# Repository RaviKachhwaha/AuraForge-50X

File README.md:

<h1 align="center">
  <br>

  <br>
  AuraForge-50X
  <br>
</h1>
<h3 align="center">
A fully open-sourced complete wireless sound computer. 
</h3>

| Front Render | Back Render | 
| --- | --- |
|  |  | 

## Schematics  

Here are the schematic design,

## Features
- **ESP32-WROOM-32E MCU** - Dual-core Xtensa LX6, adjustable from 80 MHz to 240 MHz.
- **A 50Hz Wi-Fi CSI radar and real time DSP**.
- **TPA3116D2 Class-D amp**.
- **3A fast charging with BMS and Li-ion/LiPo both Battery support**.
- Power and battery indicator LED.
- Cyberpunk Web HUD.
- **USB C** - for programming.
- A 12-21V DC jack for power.

## PCB Design 
|  |
|--- |  

 ### The PCB is 4 layers with dimensions 100x80mm, made to be easily useable for anyone.  

 ### All the PCB files are [here](https://github.com/RaviKachhwaha/AuraForge-50X/blob/main/hardware) 

| Front Layer | Inner Layer 1 |
| --- | --- |
|  |  |
| Inner Layer 2 | Bottom layer |
|  |  |

## Pinout  

This is a general pinout 

|  | 
| --- | 

## 3D image of board case 

This is a 3D view screenshot of case for board.

|  | 
| --- | 

## 3D image of speakers case 

This is a 3D view screenshot of case for speakers.

|  | 
| --- | 

Note :- I not use 3D printing for case of speakers and not added to BOM list due to the cost is very high but if any one want to get this 3D they will get files in 3D files folder.

(Credits to the KiCad EDA for KICAD 10, Espressif Systems for the MCU, RuView for CSI processing and Hack Club for fund to make this possible.) 

(Thanks to Madhav, tty7 to review my Design and tell me some mistakes like the antenna is pleased on board without open air due to that the range of it is low after the review from them I places the antenna in open air to get full range of Bluetooth and correct Wi-Fi CSI) 

## Why was it made?  

While using the normal Bluetooth amp for my many projects and in daily need, I realised it doesn't have Wi-Fi and high power support and I couldn't use it, unfortunately I had to think to buy a different high power amp then I see that those have high power but not Wi-Fi support and use very low price components which give low quality, but now I designed one with the simplicity of ESP32-WROOM-32E with being able to use Wi-Fi and Bluetooth both and also Programing support in a same board with high quality audio support for amp IC and have too many features.

## How you can get one for yourself? 

That is pretty easy, you have all the files you will need in the production folder, order the development  
board from any PCB fab ( I chose PCB Power cause its cheap in India and has good quality and also made in India ) and BINGO! You will have it to use for any purpose you want!  

## How do you use it?  
You can use it as any normal amp board but first want to flash the firmware which is given in firmware folder, for flashing you need to first enter the boootloader mode by holding the BOOT buttom and one time press and release the RESET button while connecting to your device, flash it with firmware and after all flashing done press the RESET button one time and you are good to go!
I have attached a simple firmware to start with prebuild firmware available in the firmware folder.  

## BOM  
|Name|Purpose          |Quantity|Total Cost (USD)|Link               |Distributor|
|----|-----------------|--------|----------------|-------------------|-----------|
|PCBA|Board and Assembly|2       |62.12           |[Lion Circuits](lioncircuits.com)|Lion Circuits     |
|Electronic Components|BOM Component Sourcing|2       |117.00           |[Lion Circuits](lioncircuits.com)|Lion Circuits     |
|2 Components|2 BOM Component Sourcing which is not got from Lion Circuits|2       |2.59           |[Sharvi Electronics](sharvielectronics.com)|Sharvi Electronics     |
|Battery|18650 3.7V 3000mAh Li-ion Battery with Connector for testing|1       |5.00          |[18650 Battery](https://www.amazon.in/gp/product/B0HBPWY1CS/ref=ox_sc_act_title_3?smid=AJWV8HAM5L3YL&psc=1)|Amazon India     |
|Speaker|5 Inch 4 Ohm 25W Full-Range Woofer Speaker (Stereo Pair) for testing|1       |5.48           |[5 Inch Speaker](https://www.amazon.in/gp/product/B0D8CVNZVK/ref=ox_sc_act_title_2?smid=A3C7Z4RVM9A3G1&psc=1)| Amazon India     |
|Data & Power Cable|100W USB-C to USB-C Silicone Cable (3ft / 1.0m) for uploading firmware|1       |5.00           |[USB-C Cable](https://www.amazon.in/gp/product/B0F316KC1Q/ref=ox_sc_act_title_4?smid=AJ6SIZC8YQDZX&psc=1)| Amazon India     |
|Speaker connection Cable|20 Meter speaker wiring Cable (64ft / 20.0m) for connecting the speakers and testing|1       |3.10           |[20 Meter Wire](https://www.amazon.in/gp/product/B0CHBFB5H2/ref=ox_sc_act_title_1?smid=A2LH9DQUAZIHP2&psc=1)| Amazon India     |
|Aux Cable|5 Meter Aux Cable for testing the 3.5 mm Aux jack and wired audio input system|1       |2.70           |[5 Meter Aux Cable](https://www.amazon.in/gp/product/B08XBFV4VR/ref=ox_sc_act_title_2?smid=A2LH9DQUAZIHP2&psc=1)| Amazon India     |
|Power Supply|20 Volt Power supply to run the board on its high power to test all things is working on its full power|1       |5.55           |[20V Power Supply](https://www.amazon.in/gp/product/B0D22W62W9/ref=ox_sc_act_title_1?smid=A2QFGJBWFSGOIU&psc=1)| Amazon India     |
|Cable to give power to power supply|1.5 Meter Power Cable to give power to power supply adapter due to it not have cable with it|1       |1.60           |[Main Power cable](https://www.amazon.in/gp/product/B0F9VD5NC5/ref=ox_sc_act_title_1?smid=AJ6SIZC8YQDZX&psc=1)| Amazon India     |
|3D Printing|3D printing of cases of board only|2       |17.00           |[3D Printing Service](https://3ding.in)|3Ding    |
|MDF Board |MDF board to make speakers cases|1       |2.65           |[MDF Board](https://www.amazon.in/gp/product/B09PLC82L1/ref=ox_sc_act_image_3?smid=A1URIIGAKCXMM9&psc=1)| Amazon India    |
|Fevicol|Fevicol to joint the MDF boards and make cases|1       |1.10           |[Fevicol](https://www.amazon.in/gp/product/B0FR92PQHL/ref=ox_sc_act_image_1?smid=AJ6SIZC8YQDZX&psc=1)| Amazon India    |
|Soldering Iron |Temperature controlled soldering iron to solder the 2 IC's come from Sharvi Electronics on both boards with Flux paste and extra soldering bits tips to get SMD level small tip and tweezers to hold the IC over its place without burning fingers and some other small needed items|1       |5.10           |[Soldering Iron](https://www.amazon.in/gp/product/B09Q1DNJMH/ref=ox_sc_act_image_2?smid=A1ABQHFG9A1NPH&psc=1)| Amazon India    |
|Paint |Paint is needed to paint the MDF board cases and making its life long and best quality|1       |2.25           |[Paint](https://www.amazon.in/gp/product/B08G54WH1J/ref=ox_sc_act_image_1?smid=AJ6SIZC8YQDZX&psc=1)| Amazon India    |
|Breathable Knitted Air Mesh Polyester Fabric |Net to place over the speaker case front to cover the speaker and making the case best and complete| 1       |3.10           |[Speaker Front Net](https://www.amazon.in/gp/product/B0GX12PGCJ/ref=ox_sc_act_image_2?smid=A3B565BTI4IG0&psc=1)| Amazon India    |
|24V DC RS795 Large Torque High Power Universal Motor |This is needed to cut the MDF board in required size and for hole's in MDF speaker case| 1       |3.75           |[RS795](https://www.amazon.in/gp/product/B0DVSYSMTV/ref=ox_sc_act_image_7?smid=A3C7Z4RVM9A3G1&psc=1)| Amazon India    |
|Drill Chuck For 775 Motor |This is needed to connect the cutter blades and drill bits to the RS795 motor| 1       |4.25           |[Drill Chuck](https://www.amazon.in/gp/product/B09FSN8MWR/ref=ox_sc_act_image_8?smid=AGBMZOA8TJT82&psc=1)| Amazon India    |
|HSS Circular Saw Blade/Cutting Discs Set |This is to connect in Motor and cut the MDF board in needed shape's| 1       |2.25           |[Cutting Discs](https://www.amazon.in/gp/product/B07BT39DQT/ref=ox_sc_act_image_6?smid=A14ZM8X9CLFWBZ&psc=1)| Amazon India    |
|0.3-1.6mm Shank Twist Drill Bit Set |This Drill bits is to make holes for speaker screws to fit speaker in case's| 1       |2.50           |[Drill Bit's](https://www.amazon.in/gp/product/B09CGPJSRG/ref=ox_sc_act_image_5?smid=A22JYHMKEZ67RF&psc=1)| Amazon India    |
|Adjustable Wood Hole saw Circle drill bit |This is a adjustable wood cutter (30-200mm) to cut 5 inch speaker circle hole in MDF board for speakers case's| 1       |3.65           |[Circle drill bit](https://www.amazon.in/gp/product/B0GV7VG341/ref=ox_sc_act_image_4?smid=AVW5MVBH0F2Y1&psc=1)| Amazon India    |
|5-piece CYL-1 Masonry Drill Bit Set |These are big size drill bit's to make big holes for wires and etc. in MDF speaker case's| 1       |2.75           |[Big Drill Bit's](https://www.amazon.in/gp/product/B00863NRHQ/ref=ox_sc_act_image_3?smid=AJ6SIZC8YQDZX&psc=1)| Amazon India    |
|Safety Gloves |These are for heavy duty cutting and drilling time safety and also safety from spray paint during MDF speaker cases painting and coating| 1       |3.85           |[Safety Gloves](https://www.amazon.in/gp/product/B0CHFP47WB/ref=ox_sc_act_image_2?smid=AB4PAYFSMOP1X&psc=1)| Amazon India    |
|Safety Mask with Respirator |This is for safety of eyes during spray paint and cutting and drilling and also safety of respiratory system from spray paint gas's and small particles of MDF during cutting and drilling| 1       |5.75           |[Safety Mask](https://www.amazon.in/gp/product/B0GCSJ1299/ref=ox_sc_act_image_1?smid=A2X8WL6YI17S5T&psc=1)| Amazon India    |
| | | Total | 270.80 |

LCSC & DigiKey BOM for the components on board is [here](https://github.com/RaviKachhwaha/AuraForge-50X/blob/main/components_bom.csv)

!!Thanks to ALL!!

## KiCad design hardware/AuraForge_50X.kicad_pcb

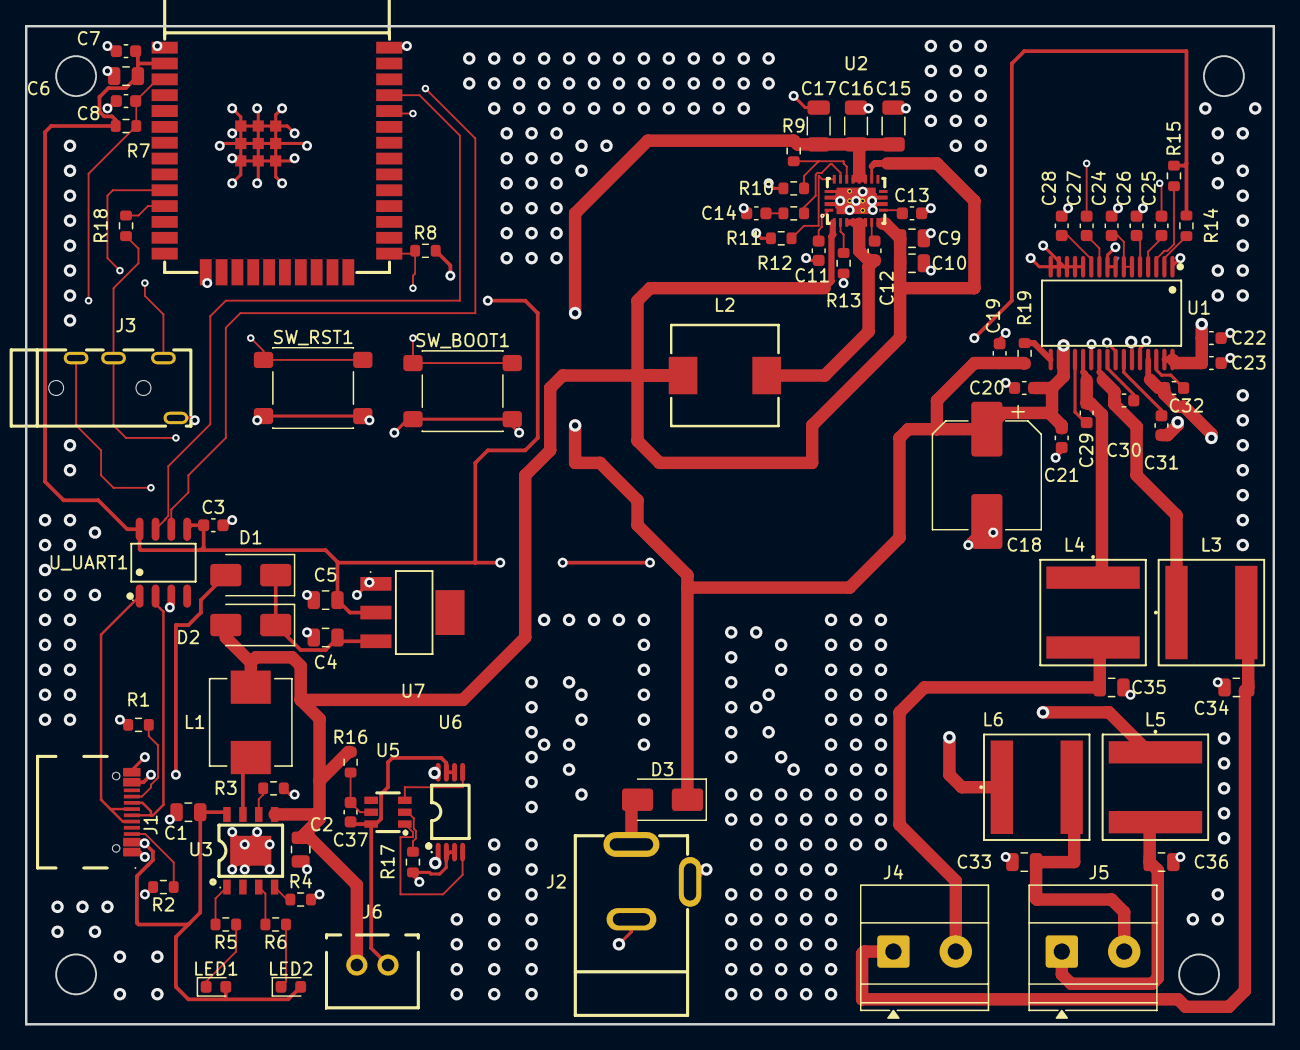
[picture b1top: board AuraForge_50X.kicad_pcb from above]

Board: 4 copper layers, 100.0 x 80.0 mm, 83 parts (0 on the bottom side), 61 nets.

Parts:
C1: 10uF 25V; C_0805_2012Metric
C2, C9, C10: 22uF 10V; C_0805_2012Metric
C3, C7, C8, C37: 100nF 16V; C_0603_1608Metric
C4: 10uF 16V; C_0805_2012Metric
C5: 22uF 6.3V; C_0805_2012Metric
C6: 10uF 10V; C_0805_2012Metric
C11, C24, C25, C26, C27, C28: 1uF 16V; C_0603_1608Metric
C12: 100nF 25V; C_0603_1608Metric
C13: 10nF 25V; C_0603_1608Metric
C14: 2.2nF 25V; C_0603_1608Metric
C15, C16, C17: 22uF 25V; C_1206_3216Metric
C18: 220uF 25V Low-ESR; CP_Elec_8x10.5
C19, C20, C21, C22, C23: 1uF 25V; C_0603_1608Metric
C29, C30, C31, C32: 0.22uF 25V; C_0603_1608Metric
C33, C34, C35, C36: 0.68uF 25V; C_0805_2012Metric
D1, D2, D3: SS34; D_SMA
J1: TYPE-C-31-M-12; USB-C_SMD-TYPE-C-31-M-12_1
J2: PJ-002AH; DC-IN-TH_PJ-002AH
J3: PJ-320A; AUDIO-TH_XKB_PJ-320A
J4: Speaker_Left; TerminalBlock_Phoenix_MKDS-1,5-2_1x02_P5.00mm_Horizontal
J5: Speaker_Right; TerminalBlock_Phoenix_MKDS-1,5-2_1x02_P5.00mm_Horizontal
J6: B2B-XH-A; CONN-TH_B2B-XH-A-LF-SN
L1: 2.2uH 6.5A; INDM7066X300N
L2: 2.2uH 10A; WE-HCC_8070
L3, L4, L5, L6: 10uH 3.8A; IND_TAIYO_NRS8040_TAY
LED1: RED; LED_0603_1608Metric
LED2: Green; LED_0603_1608Metric
R1, R2: 5.1k; R_0603_1608Metric
R3: 45k 1%; R_0603_1608Metric
R4: 51k; R_0603_1608Metric
R5, R6, R17, R18: 1k; R_0603_1608Metric
R7, R8, R11: 10k; R_0603_1608Metric
R9: 91k 1%; R_0603_1608Metric
R10: 10k 1%; R_0603_1608Metric
R12, R14, R15: 100k; R_0603_1608Metric
R13: 120k; R_0603_1608Metric
R16: 100R; R_0603_1608Metric
R19: 10R; R_0603_1608Metric
SW_BOOT1: BOOT; SW_SPST_PTS645Sx43SMTR92
SW_RST1: RESET; SW_SPST_PTS645Sx43SMTR92
U1: TPA3116D2DAD; HTSSOP-32_L11.0-W6.1-P0.65-LS8.1-BL
U2: TPS61088RHLR; VQFN-20_L4.6-W3.6-P0.50-BL
U3: IP2312-4V35; ESOP-8_L4.9-W3.9-P1.27-LS6.0-BL-EP
U4: ESP32-WROOM-32E; WIFI-SMD_ESP32-WROOM-32E
U5: DW01A-G; SOT-23-6_L2.9-W1.6-P0.95-LS2.8-BR
U6: FS8205A; TSSOP-8_L4.4-W3.0-P0.65-LS6.4-BL-2
U7: AMS1117-3.3; SOT-223-3_L6.5-W3.4-P2.30-LS7.0-BR
U_UART1: CH340N_C2977777; SOP-8_L4.9-W3.9-P1.27-LS6.0-BL

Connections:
/+3V3_SYS: C3.1, C5.2, C6.2, C7.2, R7.1, R8.2, R14.1, R15.1, U4.2 (3V3), U7.2 (VOUT), U_UART1.5 (VCC), U_UART1.8 (V3)
/+5V_VBUS: C1.1, D1.2 (A), J1.A4B9 (VBUS), J1.B4A9 (VBUS), LED1.2 (A), LED2.2 (A), U3.8 (VIN)
/+21V_BOOST: C15.1, C16.1, C17.1, C18.1, C19.1, C20.1, C21.1, C22.1, C23.1, D3.1 (K), R9.2, R19.1, U1.18 (PVCC), U1.19 (PVCC), U1.31 (PVCC), U1.32 (PVCC), U2.14 (VOUT), U2.15 (VOUT), U2.16 (VOUT)
/+BAT_3V7: C2.1, C9.1, C10.2, D2.2 (A), J6.1, L1.2, L2.1, R16.2, U2.2 (EN), U2.9 (VIN), U2.13 (MODE), U3.5 (BAT)
/AUDIO_L: C27.1, J3.2
/AUDIO_R: C25.1, J3.3, R18.1
/BAT_NEG: C37.1, J6.2, U5.6 (GND), U6.6 (S2), U6.7 (S2)
/DAC_OUT_L: J3.4, U4.10 (IO25)
/DAC_OUT_R: R18.2, U4.11 (IO26)
/ESP_EN: C8.2, R7.2, SW_RST1.1, U4.3 (EN)
/ESP_IO0: R8.1, SW_BOOT1.1, U4.25 (IO0)
/ESP_RXD0: U4.34 (RXD0), U_UART1.6 (TXD)
/ESP_TXD0: U4.35 (TXD0), U_UART1.7 (RXD)
/SPK_L_MINUS: C35.1, J4.2, L4.2
/SPK_L_PLUS: C34.1, J4.1, L3.2
/SPK_R_MINUS: C33.1, J5.2, L6.2
/SPK_R_PLUS: C36.1, J5.1, L5.2
/USB_DN: J1.A7 (DN1), J1.B7 (DN2), U_UART1.2 (UD-)
/USB_DP: J1.A6 (DP1), J1.B6 (DP2), U_UART1.1 (UD+)
/V_LDO_IN: C4.2, D1.1 (K), D2.1 (K), U7.3 (VIN)
GND: C1.2, C2.2, C3.2, C4.1, C5.1, C6.1, C7.1, C8.1, C9.2, C10.1, C11.1, C13.2, C14.2, C15.2, C16.2, C17.2, C18.2, C19.2, C20.2, C21.2, C22.2, C23.2, C24.1, C26.1, C28.1, C33.2, C34.2, C35.2, C36.2, J1.A1B12 (GND), J1.B1A12 (GND), J2.2, J2.3, J3.5, R1.2, R2.2, R3.2, R4.2, R10.2, R12.1, R13.1, R17.2, SW_BOOT1.2, SW_RST1.2, U1.1 (MODSEL), U1.8 (GAIN/SLV), U1.9 (GND), U1.12 (MUTE), U1.13 (AM2), U1.14 (AM1), U1.15 (AM0), U1.16 (SYNC), U1.22 (GND), U1.25 (GND), U1.28 (GND), U2.20 (AGND), U2.21 (PGND), U3.9 (EP), U4.1 (GND), U4.15 (GND), U4.38 (GND), U4.39 (GND), U6.2 (S1), U6.3 (S1), U7.1 (GND), U_UART1.3 (GND)
unnamed: C12.2, L2.2, U2.4 (SW), U2.5 (SW), U2.6 (SW), U2.7 (SW)
unnamed: C14.1, R11.2
unnamed: D3.2 (A), J2.1
unnamed: J1.A5 (CC1), R1.1
unnamed: J1.B5 (CC2), R2.1
unnamed: LED1.1 (K), R5.1
unnamed: LED2.1 (K), R6.1
unnamed: R19.2, U1.17 (AVCC)
unnamed: C29.2, U1.20 (BSNL)
unnamed: C31.2, U1.26 (BSNR)
unnamed: C30.1, U1.24 (BSPL)
unnamed: C32.1, U1.30 (BSPR)
unnamed: R15.2, U1.3 (FAULTZ)
unnamed: C24.2, U1.6 (PLIMIT), U1.7 (GVDD)
unnamed: C28.2, U1.11 (LINN)
unnamed: C27.2, U1.10 (LINP)
unnamed: C29.1, L4.1, U1.21 (OUTNL)
unnamed: C31.1, L6.1, U1.27 (OUTNR)
unnamed: C30.2, L3.1, U1.23 (OUTPL)
unnamed: C32.2, L5.1, U1.29 (OUTPR)
unnamed: C26.2, U1.5 (RINN)
unnamed: C25.2, U1.4 (RINP)
unnamed: R14.2, U1.2 (SDZ)
unnamed: C12.1, U2.8 (BOOT)
unnamed: R11.1, U2.18 (COMP)
unnamed: R9.1, R10.1, U2.17 (FB)
unnamed: R13.2, U2.3 (FSW)
unnamed: R12.2, U2.19 (ILIM)
unnamed: C13.1, U2.10 (SS)
unnamed: C11.2, U2.1 (VCC)
unnamed: R5.2, U3.1 (D1)
unnamed: R6.2, U3.3 (D2)
unnamed: R3.1, U3.6 (ICHG)
unnamed: R4.1, U3.4 (NTC)
unnamed: L1.1, U3.7 (SW)
unnamed: R17.1, U5.2 (CS)
unnamed: U5.3 (OC), U6.5 (G2)
unnamed: U5.1 (OD), U6.4 (G1)
unnamed: C37.2, R16.1, U5.5 (VCC)
unnamed: U6.1 (D12), U6.8 (D12)

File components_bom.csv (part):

Item #,Reference,Qty,Value,Description,Footprint,Manufacturer,MPN,LCSC Part,Unit Price (₹),Unit Price ($),Total Price (₹),Total Price ($),Supplier Link
1,C1,1,10uF 25V,MLCC Ceramic Capacitor 10uF 25V X7S 0805 for Boost/Buck Input Filtering,Capacitor_SMD:C_0805_2012Metric,TDK,C2012X7S1E106K125AC,,56.37,0.5911,56.37,0.59,https://www.digikey.in/en/products/detail/tdk/C2012X7S1E106K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
2,"C2, C9, C10",3,22uF 10V,MLCC Ceramic Capacitor 22uF 10V X5R 0805 for 3.3V/5V Rail Bulk Decoupling,Capacitor_SMD:C_0805_2012Metric,Yageo,CC0805MKX5R6BB226,,44.91,0.4709,134.73,1.41,https://www.digikey.in/en/products/detail/yageo/CC0805MKX5R6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
3,"C3, C7, C8, C37",4,100nF 16V,MLCC Ceramic Capacitor 100nF 16V X7R 0603 High-Frequency Bypass Decoupling,Capacitor_SMD:C_0603_1608Metric,Yageo,CC0603KRX7R7BB104,,9.56,0.1002,38.24,0.40,https://www.digikey.in/en/products/detail/yageo/CC0603KRX7R7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
4,C4,1,10uF 16V,MLCC Ceramic Capacitor 10uF 16V X5R 0805 Power Rail Decoupling,Capacitor_SMD:C_0805_2012Metric,Yageo,CC0805KRX5R7BB106,,60.20,0.6312,60.20,0.63,https://www.digikey.in/en/products/detail/yageo/CC0805KRX5R7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
5,C5,1,22uF 6.3V,MLCC Ceramic Capacitor 22uF 6.3V X5R 0805 Low-Voltage Rail Filter,Capacitor_SMD:C_0805_2012Metric,Yageo,CC0805MKX5R5BB226,,40.13,0.4208,40.13,0.42,https://www.digikey.in/en/products/detail/yageo/CC0805MKX5R5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
6,C6,1,10uF 10V,MLCC Ceramic Capacitor 10uF 10V X5R 0805 LDO Output Filter,Capacitor_SMD:C_0805_2012Metric,Yageo,CC0805KRX5R6BB106,,51.60,0.5411,51.60,0.54,https://www.digikey.in/en/products/detail/yageo/CC0805KRX5R6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
7,"C11, C24, C25, C26, C27, C28",6,1uF 16V,MLCC Ceramic Capacitor 1uF 16V X7R 0603 AC Audio Input Coupling & Decoupling,Capacitor_SMD:C_0603_1608Metric,Yageo,CC0603KRX7R7BB105,,16.24,0.1703,97.44,1.02,https://www.digikey.in/en/products/detail/yageo/CC0603KRX7R7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
8,C12,1,100nF 25V,MLCC Ceramic Capacitor 100nF 25V X7R 0603 High-Voltage Bootstrap Bypass,Capacitor_SMD:C_0603_1608Metric,Yageo,CC0603KRX7R8BB104,,9.56,0.1002,9.56,0.10,https://www.digikey.in/en/products/detail/yageo/CC0603KRX7R8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
9,C13,1,10nF 25V,MLCC Ceramic Capacitor 10nF 25V X7R 0603 Snubber & High-Frequency Filter,Capacitor_SMD:C_0603_1608Metric,Yageo,CC0603KRX7R8BB103,,9.56,0.1002,9.56,0.10,https://www.digikey.in/en/products/detail/yageo/CC0603KRX7R8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
10,C14,1,2.2nF 25V,MLCC Ceramic Capacitor 2.2nF 25V X7R 0603 Filter & Timing Network,Capacitor_SMD:C_0603_1608Metric,Yageo,CC0603KRX7R8BB222,,9.56,0.1002,9.56,0.10,https://www.digikey.in/en/products/detail/yageo/CC0603KRX7R8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
11,"C15, C16, C17",3,22uF 25V,MLCC Ceramic Capacitor 22uF 25V X5R 1206 High-Voltage Output Filter,Capacitor_SMD:C_1206_3216Metric,Samsung,CL31A226KAHNNNE,,36.31,0.3807,108.93,1.14,https://www.digikey.in/en/products/detail/samsung-electro-me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
12,C18,1,220uF 25V Radial 8x10.5,Aluminum Electrolytic Capacitor 220uF 25V Radial 8x10.5mm for Power Stage Reservoir,Capacitor_SMD:CP_Elec_8x10.5,Würth Elektronik,865060453007,,69.75,0.7314,69.75,0.73,https://www.digikey.in/en/products/detail/w%C3%BCrth-elektro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
13,"C19, C20, C21, C22, C23",5,1uF 25V,MLCC Ceramic Capacitor 1uF 25V X7R 0603 Bootstrap & Bias Decoupling,Capacitor_SMD:C_0603_1608Metric,Yageo,CC0603KPX7R8BB105,,9.62,0.1009,48.10,0.50,https://www.digikey.in/en/products/detail/yageo/CC0603KPX7R8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
14,"C29, C30, C31, C32",4,0.22uF 25V,MLCC Ceramic Capacitor 0.22uF 25V X7R 0603 Bootstrap Capacitors for Class-D Stage,Capacitor_SMD:C_0603_1608Metric,Yageo,CC0603KRX7R8BB224,,15.29,0.1603,61.16,0.64,https://www.digikey.in/en/products/detail/yageo/CC0603KRX7R8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
15,"C33, C34, C35, C36",4,0.68uF 25V,MLCC Ceramic Capacitor 0.68uF 25V X7R 0805 LC Output Filter Reconstruction,Capacitor_SMD:C_0805_2012Metric,Yageo,CC0805KKX7R9BB684,,27.71,0.2906,110.84,1.16,https://www.digikey.in/en/products/detail/yageo/CC0805KKX7R9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
16,"D1, D2, D3",3,SS34 (3A 40V),Schottky Barrier Diode 3A 40V SMA for Reverse Polarity & Power Path Protection,Diode_SMD:D_SMA,onsemi,MBRA340T3G,,90.77,0.9518,272.31,2.86,https://www.digikey.in/en/products/detail/onsemi/MBRA340T3G/918606
17,J1,1,TYPE-C-31-M-12,USB Type-C 16-Pin Receptacle with SMT + Through-Hole Shield Tabs for Power & Flashing,easyeda2kicad:USB-C_SMD-TYPE-C-31-M-12_1,GCT,USB4105-GF-A,C165948,76.44,0.8015,76.44,0.80,https://www.digikey.in/en/products/detail/gct/USB4105-GF-A/11198441
18,J2,1,PJ-002AH,DC Power Barrel Jack 5.5mm x 2.1mm Through-Hole for 12V-21V External Power Input,easyeda2kicad:DC-IN-TH_PJ-002AH,CUI Devices,PJ-002AH,C2961147,67.84,0.7113,67.84,0.71,https://www.digikey.in/en/products/detail/same-sky-formerly-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
19,J3,1,PJ-320A,3.5mm Stereo Audio Headphone Jack 5-Pin Through-Hole Connector,easyeda2kicad:AUDIO-TH_XKB_PJ-320A,CUI Devices,SJ-3524-SMT-TR,C2884926,85.04,0.8917,85.04,0.89,https://www.digikey.in/en/products/detail/same-sky-formerly-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
20,"J4, J5",2,Speaker_Terminal,2-Pin 5.08mm Pitch Screw Terminal Block for Left & Right Speaker Output Connections,"TerminalBlock_Phoenix:TerminalBlock_Phoenix_MKDS-1,5-2_1x02_P5.00mm_Horizontal",Phoenix Contact,1715721,,110.84,1.1622,221.68,2.32,https://www.digikey.in/en/products/detail/phoenix-contact/17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
21,J6,1,B2B-XH-A,2-Pin 2.5mm Pitch JST-XH Keyed Battery Connector for 3.7V Li-ion Connection,easyeda2kicad:CONN-TH_B2B-XH-A-LF-SN,JST,B2B-XH-A(LF)(SN),C158012,9.56,0.1002,9.56,0.10,https://www.digikey.in/en/products/detail/jst-sales-america-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
22,L1,1,2.2uH 6.5A,Shielded Power Inductor 2.2uH 6.5A SMD 7.3x7.3mm for IP2312 3A Buck Charger,Inductor_SMD:L_7.3x7.3_H4.5,Shenzhen Sunlord Electronics Co. Ltd.,MWSA0603S-2R2MT,,93.64,0.9819,93.64,0.98,https://www.digikey.in/en/products/detail/shenzhen-sunlord-e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
23,L2,1,2.2uH 10.0A,High-Current Shielded Power Inductor 2.2uH 10.0A SMD 10.4x10.4mm for TPS61088 Boost,Inductor_SMD:L_10.4x10.4_H4.8,Wurth Elektronik,7443340220,,204.48,2.1441,204.48,2.14,https://www.digikey.in/en/products/detail/w%C3%BCrth-elektro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
24,"L3, L4, L5, L6",4,10uH 3.8A,Shielded Power Inductors 10uH 3.8A SMD 8.0x8.0mm for TPA3116D2 LC Output Filter,Inductor_SMD:L_Taiyo-Yuden_NR-80xx,Taiyo Yuden,NRS8040T100MJGJ,,33.44,0.3506,133.76,1.40,https://www.digikey.in/en/products/detail/taiyo-yuden/NRS804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
25,LED1,1,Red LED (Charge),Surface Mount Red LED 0603 Indicator for Battery Charging Status,LED_SMD:LED_0603_1608Metric,Kingbright,APT1608SURCK,,20.06,0.2103,20.06,0.21,https://www.digikey.in/en/products/detail/kingbright/APT1608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
26,LED2,1,Green LED (Done),Surface Mount Green LED 0603 Indicator for Charge Complete / Standby Status,LED_SMD:LED_0603_1608Metric,Kingbright,APT1608ZGC,,60.20,0.6312,60.20,0.63,https://www.digikey.in/en/products/detail/kingbright/APT1608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
27,"R1, R2",2,5.1k 1%,Thick Film Chip Resistor 5.1k Ohm 1% 0603 for USB Type-C CC1/CC2 Pull-Down Configuration,Resistor_SMD:R_0603_1608Metric,Yageo,RC0603FR-135K1L,,9.56,0.1002,19.12,0.20,https://www.digikey.in/en/products/detail/yageo/RC0603FR-135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
28,R3,1,45.3k 1%,Thick Film Chip Resistor 45.3k Ohm 1% 0603 for Fast Charger Configuration,Resistor_SMD:R_0603_1608Metric,Yageo,RC0603FR-0745K3L,,9.56,0.1002,9.56,0.10,https://www.digikey.in/en/products/detail/yageo/RC0603FR-074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
29,R4,1,51k 1%,Thick Film Chip Resistor 51k Ohm 1% 0603 for Status & Bias Circuitry,Resistor_SMD:R_0603_1608Metric,Yageo,RC0603FR-1351KL,,9.56,0.1002,9.56,0.10,https://www.digikey.in/en/products/detail/yageo/RC0603FR-135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
30,"R5, R6, R17, R18",4,1k 1%,Thick Film Chip Resistor 1k Ohm 1% 0603 for LED Current Limiting & Bias,Resistor_SMD:R_0603_1608Metric,Yageo,RC0603FR-071KL,,9.56,0.1002,38.24,0.40,https://www.digikey.in/en/products/detail/yageo/RC0603FR-071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
31,"R7, R8, R10, R11",4,10k 1%,Thick Film Chip Resistor 10k Ohm 1% 0603 for I2C/Pull-up/Feedback Divider Networks,Resistor_SMD:R_0603_1608Metric,Yageo,RC0603FR-0710KL,,9.56,0.1002,38.24,0.40,https://www.digikey.in/en/products/detail/yageo/RC0603FR-071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
32,R9,1,91k 1%,Thick Film Chip Resistor 91k Ohm 1% 0603 for TPS61088 12.0V Feedback Voltage Divider,Resistor_SMD:R_0603_1608Metric,Yageo,RC0603FR-0791KL,,9.56,0.1002,9.56,0.10,https://www.digikey.in/en/products/detail/yageo/RC0603FR-079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
